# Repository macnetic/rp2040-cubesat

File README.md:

# rp2040-cubesat

> [!NOTE]  
> Preview this project on your browser with [KiCanvas](https://kicanvas.org/?github=https%3A%2F%2Fgithub.com%2Fmacnetic%2Frp2040-cubesat)!

## Requirements

| ID  | DESCRIPTION |
|-----|-------------|
| 001 | Device shall include a minimum of one RP2040 integrated circuit. |
| 002 | Dimensions shall conform with PCI/104 form factor. |
| 003 | Device shall supply 1 external UART interface. |
| 004 | Device shall supply 1 external CAN interface. |
| 005 | Device shall supply 1 on-board SPI interface. |
| 006 | Device shall supply 1 on-board I2C interface. |
| 007 | Device shall use a TCXO to generate a stable reference clock. |

## External interfaces

- UART (PHY TBD)
- CAN
- ARM CoreSight-10

## Schematic strategy

The schematics for this project is laid out across multiple sheets. 
The top-level sheets contain functional block diagrams. 
The functional circuit blocks themselves are implemented in the lower-level sheets.

## PCB Layout strategy

A 4-layer controlled impedance stackup is used.

|Layer       | Designation |
|------------|-------------|
| L1 (Top)   | SIG         |
| L2         | GND         |
| L3         | GND         |
| L3 (Bottom)| SIG+PWR     |

Functional circuit blocks are routed first. The blocks are then laid out and connected.

High-speed electrical interfaces are routed with controlled impedance transmission lines.

Priority is given to routing high-speed interfaces.

Sensitive analog circuitry is separated from digital circuitry.

## References

[1] [CubeSat Information - CubeSat.org](https://www.cubesat.org/cubesatinfo)

[2] [CubeSat Kit PCB Specification](https://web.archive.org/web/20220302180556/http://www.cubesatkit.com/docs/CSK_PCB_Spec-A5.pdf) (archived from the original at http://www.cubesatkit.com/docs/CSK_PCB_Spec-A5.pdf)

[3] [RP2040 Documentation](https://www.raspberrypi.com/documentation/microcontrollers/rp2040.html)

[4]

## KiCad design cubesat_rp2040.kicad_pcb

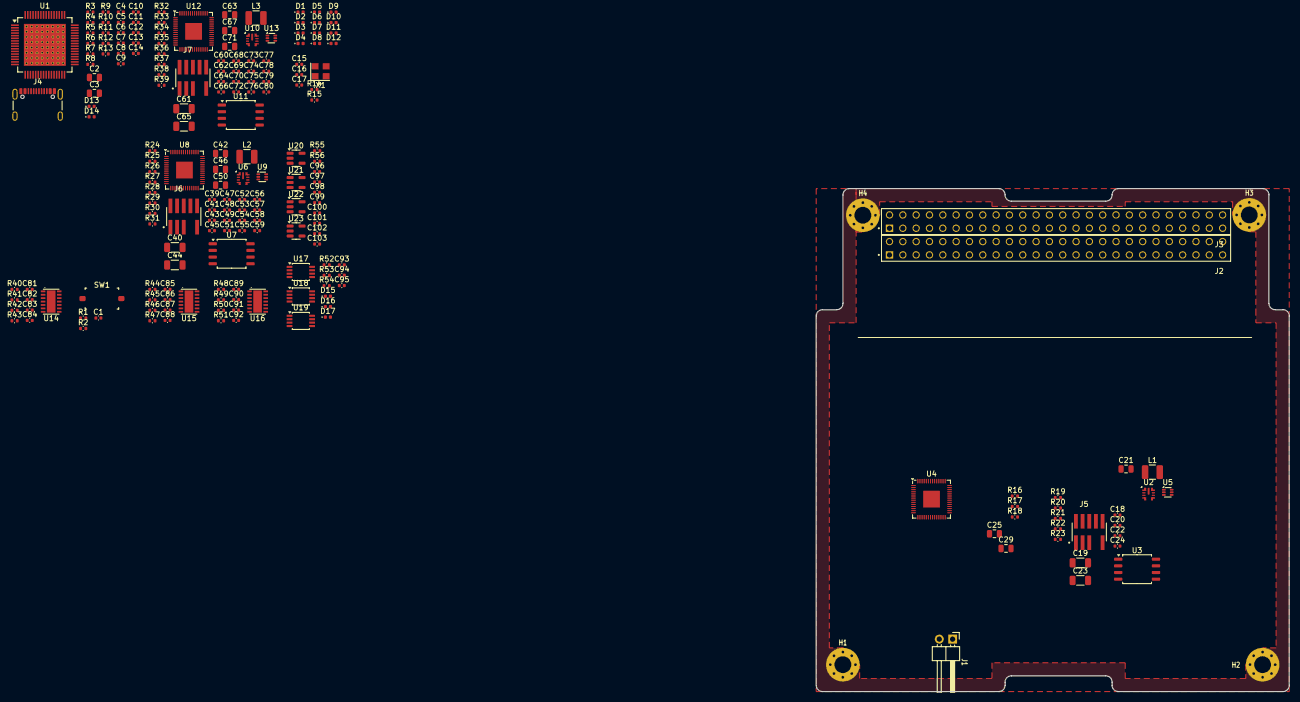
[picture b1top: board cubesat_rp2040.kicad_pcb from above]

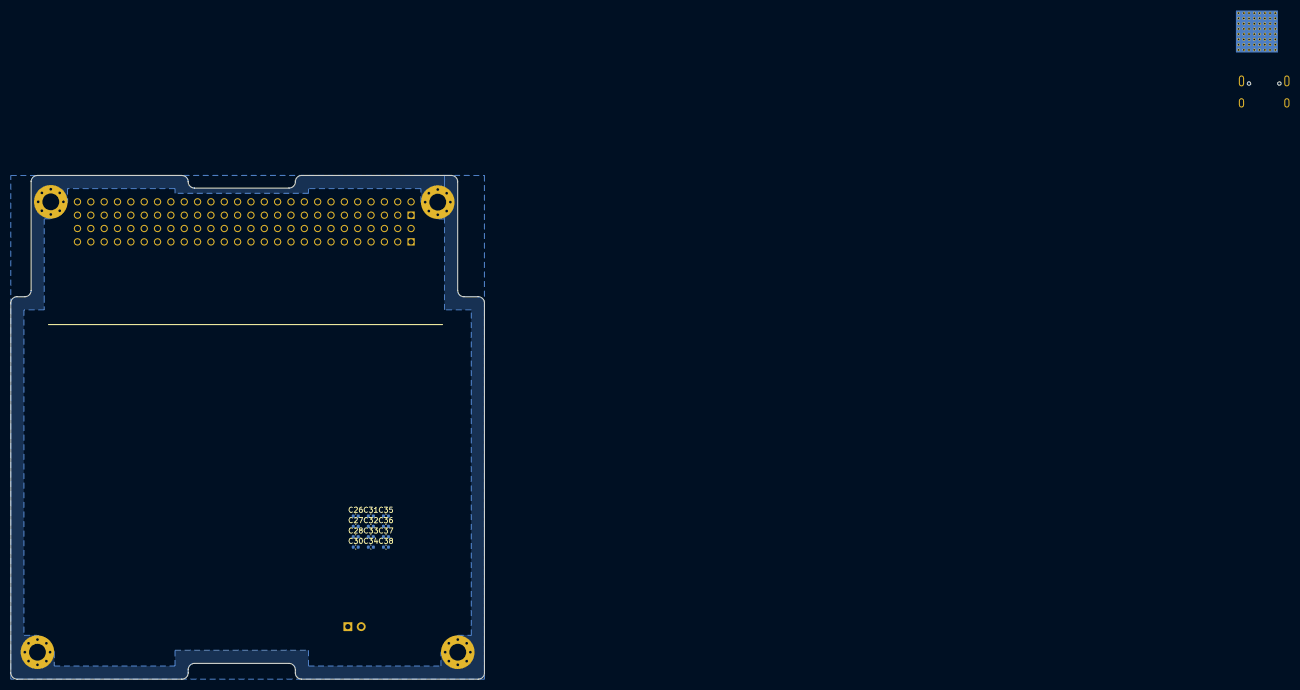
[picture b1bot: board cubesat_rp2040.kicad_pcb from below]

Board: 6 copper layers, 90.2 x 95.9 mm, 215 parts (12 on the bottom side), 138 nets, no tracks yet.

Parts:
C1, C4, C5, C6, C7, C8, C9, C10, C11, C12, C13, C14, C15, C16, C18, C20, C22, C24, C26, C27, C28, C30, C31, C32, C33, C34, C35, C36, C37, C38, C39, C41, C43, C45, C47, C48, C49, C51, C52, C53, C54, C55, C56, C57, C58, C59, C60, C62, C64, C66, C68, C69, C70, C72, C73, C74, C75, C76, C77, C78, C79, C80, C81, C82, C85, C86, C89, C90, C93, C94, C95, C96, C97, C98, C99: 100nF; C_0402_1005Metric
C2, C3, C21, C25, C29, C42, C46, C50, C63, C67, C71: 1uF; C_0805_2012Metric
C17: 15pF; C_0402_1005Metric
C19, C23, C40, C44, C61, C65: 10uF; C_1206_3216Metric
C83, C84, C87, C88, C91, C92: 4.7nF; C_0402_1005Metric
C100, C101, C102, C103: 1nF; C_0402_1005Metric
D1, D2, D3, D4, D5, D6, D7, D8, D9, D10, D11, D12, D13, D14: D_TVS; D_0402_1005Metric
D15, D16, D17: RED; LED_0402_1005Metric
H1, H2, H3, H4: MountingHole_Pad; MountingHole_3.2mm_M3_Pad_Via
J1: Conn_01x02; PinHeader_1x02_P2.54mm_Horizontal
J2, J3: ESQ-126-39-G-D; SAMTEC_ESQ-126-39-G-D_CUBESAT
J4: USB_C_Receptacle_USB2.0; USB_C_Receptacle_GCT_USB4105-xx-A_16P_TopMnt_Horizontal
J5, J6, J7: FTSH-105-01-L-DV-007-K; SAMTEC_FTSH-105-01-L-DV-007
L1, L2, L3: 15uH; L_1210_3225Metric
R1, R19, R20, R21, R22, R23, R27, R28, R29, R30, R31, R35, R36, R37, R38, R39: 100kR; R_0402_1005Metric
R2: 10kR; R_0402_1005Metric
R3, R4: 5.1kR 10%; R_0402_1005Metric
R5: 90.9kR 1%; R_0402_1005Metric
R6, R9, R10, R11, R12, R13: 4.7kR; R_0402_1005Metric
R7: 10kR 1%; R_0402_1005Metric
R8: 9.53kR 1%; R_0402_1005Metric
R14: 33R; R_0402_1005Metric
R15: 88.7R; R_0402_1005Metric
R16, R24, R32: 1kR; R_0402_1005Metric
R17, R18, R25, R26, R33, R34: 27R; R_0402_1005Metric
R40, R41, R42, R43, R44, R45, R46, R47, R48, R49, R50, R51: 60R; R_0402_1005Metric
R52, R53, R54: 470R; R_0402_1005Metric
R55, R56: 100R; R_0402_1005Metric
SW1: SW_Push; SW_Push_SPST_XKB_TS-1101-X-X
U1: TUSB4041I; HTQFP-64-1EP_10x10mm_P0.5mm_EP8x8mm_Mask4.4x4.4mm_ThermalVi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
U2, U6, U10: LMR36503MSC3RPERQ1; TI_VQFN-HR_2.1x2.1mm_P0.5mm
U3, U7, U11: IS25LP128F; SOIC-8_5.275x5.275mm_P1.27mm
U4, U8, U12: RP2040; QFN-56-1EP_7x7mm_P0.4mm_EP3.2x3.2mm
U5, U9, U13: 74LVC1G11; SOT-563
U14, U15, U16: TCAN1048AV-Q1; SOT1086-2_HVSON14_4.5x3x0.85mm_P0.65mm
U17, U18, U19: 74LVC2G38; TSSOP-8_3x3mm_P0.65mm
U20, U21: SN65LVDS1DBV; SOT-23-5
U22, U23: SN65LVDS2DBV; SOT-23-5
X1: YSO140TC; Oscillator_SMD_YXC_YSO140TC_4Pin_3.2x2.5mm

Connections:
+1V1: C2.1, C4.1, C5.1, C6.1, C7.1, C8.1, C9.1, C10.1, U1.19 (VDD), U1.25 (VDD), U1.37 (VDD), U1.45 (VDD), U1.53 (VDD), U1.60 (VDD), U1.63 (VDD)
+3V3: C3.1, C11.1, C12.1, C13.1, C14.1, C82.1, C86.1, C90.1, C93.1, C94.1, C95.1, R1.1, R14.1, R52.1, R53.1, R54.1, U1.2 (VDD33), U1.20 (VDD33), U1.31 (VDD33), U1.48 (VDD33), U14.11 (VIO), U15.11 (VIO), U16.11 (VIO), U17.8 (VCC), U18.8 (VCC), U19.8 (VCC)
+5V: C81.1, C85.1, C89.1, U14.3 (VCC), U15.3 (VCC), U16.3 (VCC)
/BOOTSEL: J1.1, R16.2, R24.2, R32.2
/CAN PHY - UNIT A/CAN_A.N: D2.2 (A2), J2.01, R41.1, R45.1, R49.1, U14.12 (CANL1), U15.12 (CANL1), U16.12 (CANL1)
/CAN PHY - UNIT A/CAN_A.P: D1.2 (A2), J2.03, R40.1, R44.1, R48.1, U14.13 (CANH1), U15.13 (CANH1), U16.13 (CANH1)
/CAN PHY - UNIT A/CAN_A.RXD: U4.16 (GPIO13), U14.4 (RXD1)
/CAN PHY - UNIT A/CAN_A.TXD: U4.17 (GPIO14), U14.1 (TXD1)
/CAN PHY - UNIT A/CAN_A.~STB: U4.18 (GPIO15), U14.14 (~STB1)
/CAN PHY - UNIT A/CAN_B.N: D4.2 (A2), J2.02, R43.1, R47.1, R51.1, U14.9 (CANL2), U15.9 (CANL2), U16.9 (CANL2)
/CAN PHY - UNIT A/CAN_B.P: D3.2 (A2), J2.04, R42.1, R46.1, R50.1, U14.10 (CANH2), U15.10 (CANH2), U16.10 (CANH2)
/CAN PHY - UNIT A/CAN_B.RXD: U4.14 (GPIO11), U14.7 (RXD2)
/CAN PHY - UNIT A/CAN_B.TXD: U4.15 (GPIO12), U14.6 (TXD2)
/CAN PHY - UNIT A/CAN_B.~STB: U4.13 (GPIO10), U14.8 (~STB2)
/CAN PHY - UNIT B/CAN_A.RXD: U8.16 (GPIO13), U15.4 (RXD1)
/CAN PHY - UNIT B/CAN_A.TXD: U8.17 (GPIO14), U15.1 (TXD1)
/CAN PHY - UNIT B/CAN_A.~STB: U8.18 (GPIO15), U15.14 (~STB1)
/CAN PHY - UNIT B/CAN_B.RXD: U8.14 (GPIO11), U15.7 (RXD2)
/CAN PHY - UNIT B/CAN_B.TXD: U8.15 (GPIO12), U15.6 (TXD2)
/CAN PHY - UNIT B/CAN_B.~STB: U8.13 (GPIO10), U15.8 (~STB2)
/CAN PHY - UNIT C/CAN_A.RXD: U12.16 (GPIO13), U16.4 (RXD1)
/CAN PHY - UNIT C/CAN_A.TXD: U12.17 (GPIO14), U16.1 (TXD1)
/CAN PHY - UNIT C/CAN_A.~STB: U12.18 (GPIO15), U16.14 (~STB1)
/CAN PHY - UNIT C/CAN_B.RXD: U12.14 (GPIO11), U16.7 (RXD2)
/CAN PHY - UNIT C/CAN_B.TXD: U12.15 (GPIO12), U16.6 (TXD2)
/CAN PHY - UNIT C/CAN_B.~STB: U12.13 (GPIO10), U16.8 (~STB2)
/Cubesat System Bus/+3V3: J2.27, J2.28
/Cubesat System Bus/+5V: J2.25, J2.26, J3.25, J3.26
/Cubesat System Bus/CHARGE: J2.31, J2.32
/Cubesat System Bus/UART_A.D+: D5.2 (A2), J2.05
/Cubesat System Bus/UART_A.D-: D6.2 (A2), J2.07
/Cubesat System Bus/UART_B.D+: D7.2 (A2), J2.06
/Cubesat System Bus/UART_B.D-: D8.2 (A2), J2.08
/Cubesat System Bus/UART_C.D+: D9.2 (A2), J2.13
/Cubesat System Bus/UART_C.D-: D10.2 (A2), J2.15
/Cubesat System Bus/UART_D.D+: D11.2 (A2), J2.22
/Cubesat System Bus/UART_D.D-: D12.2 (A2), J2.24
/Cubesat System Bus/VBAT: J3.45, J3.46
/LVDS/+3V3_UNIT: C96.1, C97.1, C98.1, C99.1, C100.1, C101.1, C102.1, C103.1, U20.1 (V_{CC}), U21.1 (V_{CC}), U22.1 (V_{CC}), U23.1 (V_{CC})
/LVDS/LVDS_RX_A.N: R55.2, U22.4 (B)
/LVDS/LVDS_RX_A.P: R55.1, U22.3 (A)
/LVDS/LVDS_RX_B.N: R56.2, U23.4 (B)
/LVDS/LVDS_RX_B.P: R56.1, U23.3 (A)
/Oscillator/24M0_CLK: C17.2, R15.2, U1.30 (XI), U4.20 (XIN), U8.20 (XIN), U12.20 (XIN)
/RP2040 - Unit A/+1V1_UNIT: C25.1, C26.1, C27.1, C28.1, U4.23 (DVDD), U4.45 (VREG_VOUT), U4.50 (DVDD)
/RP2040 - Unit A/+3V3_UNIT: C18.1, C23.1, C24.1, C29.1, C30.1, C31.1, C32.1, C33.1, C34.1, C35.1, C36.1, C37.1, C38.1, J5.01 (VTREF), L1.2, R19.2, R21.1, R22.1, R23.1, U2.8 (FB), U3.8 (VCC), U4.1 (IOVDD), U4.10 (IOVDD), U4.22 (IOVDD), U4.33 (IOVDD), U4.42 (IOVDD), U4.43 (ADC_AVDD), U4.44 (VREG_VIN), U4.48 (USB_VDD), U4.49 (IOVDD), U5.5 (VCC)
/RP2040 - Unit A/BOOT: C22.1, U2.6 (BOOT)
/RP2040 - Unit A/QSPI.SCLK: U3.6 (SCK), U4.52 (QSPI_SCLK)
/RP2040 - Unit A/QSPI.SD0: U3.5 (SI/IO0), U4.53 (QSPI_SD0)
/RP2040 - Unit A/QSPI.SD1: U3.2 (SO/IO1), U4.55 (QSPI_SD1)
/RP2040 - Unit A/QSPI.SD2: U3.3 (~WP/IO2), U4.54 (QSPI_SD2)
/RP2040 - Unit A/QSPI.SD3: U3.7 (~HOLD/IO3), U4.51 (QSPI_SD3)
/RP2040 - Unit A/QSPI.~SS: R16.1, U3.1 (~CE), U4.56 (QSPI_SS)
/RP2040 - Unit A/RP_USB.D+: R17.2, U4.47 (USB_DP)
/RP2040 - Unit A/RP_USB.D-: R18.2, U4.46 (USB_DM)
/RP2040 - Unit A/SW: C22.2, L1.1, U2.5 (SW)
/RP2040 - Unit A/SWCLK: J5.04 (TCK/SWCLK), R20.2, U4.24 (SWCLK)
/RP2040 - Unit A/SWDIO: J5.02 (TMS/SWDIO), R19.1, U4.25 (SWD)
/RP2040 - Unit A/TMR_VOTE_1: U4.38 (GPIO26_ADC0), U17.5, U18.1
/RP2040 - Unit A/TMR_VOTE_2: U4.39 (GPIO27_ADC1), U18.5, U19.1
/RP2040 - Unit A/USB.D+: R17.1, U1.56 (USB_DP_DN4)
/RP2040 - Unit A/USB.D-: R18.1, U1.57 (USB_DM_DN4)
/RP2040 - Unit A/~PWR_RESET: R22.2, U2.2 (PGOOD), U5.1
/RP2040 - Unit A/~RESET: U4.26 (RUN), U5.4
/RP2040 - Unit B/+1V1_UNIT: C46.1, C47.1, C48.1, C49.1, U8.23 (DVDD), U8.45 (VREG_VOUT), U8.50 (DVDD)
/RP2040 - Unit B/+3V3_UNIT: C39.1, C44.1, C45.1, C50.1, C51.1, C52.1, C53.1, C54.1, C55.1, C56.1, C57.1, C58.1, C59.1, J6.01 (VTREF), L2.2, R27.2, R29.1, R30.1, R31.1, U6.8 (FB), U7.8 (VCC), U8.1 (IOVDD), U8.10 (IOVDD), U8.22 (IOVDD), U8.33 (IOVDD), U8.42 (IOVDD), U8.43 (ADC_AVDD), U8.44 (VREG_VIN), U8.48 (USB_VDD), U8.49 (IOVDD), U9.5 (VCC)
/RP2040 - Unit B/BOOT: C43.1, U6.6 (BOOT)
/RP2040 - Unit B/QSPI.SCLK: U7.6 (SCK), U8.52 (QSPI_SCLK)
/RP2040 - Unit B/QSPI.SD0: U7.5 (SI/IO0), U8.53 (QSPI_SD0)
/RP2040 - Unit B/QSPI.SD1: U7.2 (SO/IO1), U8.55 (QSPI_SD1)
/RP2040 - Unit B/QSPI.SD2: U7.3 (~WP/IO2), U8.54 (QSPI_SD2)
/RP2040 - Unit B/QSPI.SD3: U7.7 (~HOLD/IO3), U8.51 (QSPI_SD3)
/RP2040 - Unit B/QSPI.~SS: R24.1, U7.1 (~CE), U8.56 (QSPI_SS)
/RP2040 - Unit B/RP_USB.D+: R25.2, U8.47 (USB_DP)
/RP2040 - Unit B/RP_USB.D-: R26.2, U8.46 (USB_DM)
/RP2040 - Unit B/SW: C43.2, L2.1, U6.5 (SW)
/RP2040 - Unit B/SWCLK: J6.04 (TCK/SWCLK), R28.2, U8.24 (SWCLK)
/RP2040 - Unit B/SWDIO: J6.02 (TMS/SWDIO), R27.1, U8.25 (SWD)
/RP2040 - Unit B/TMR_VOTE_1: U8.38 (GPIO26_ADC0), U17.1, U19.5
/RP2040 - Unit B/TMR_VOTE_2: U8.39 (GPIO27_ADC1), U18.6, U19.2
/RP2040 - Unit B/USB.D+: R25.1, U1.49 (USB_DP_DN3)
/RP2040 - Unit B/USB.D-: R26.1, U1.50 (USB_DM_DN3)
/RP2040 - Unit B/~PWR_RESET: R30.2, U6.2 (PGOOD), U9.1
/RP2040 - Unit B/~RESET: U8.26 (RUN), U9.4
/RP2040 - Unit C/+1V1_UNIT: C67.1, C68.1, C69.1, C70.1, U12.23 (DVDD), U12.45 (VREG_VOUT), U12.50 (DVDD)
/RP2040 - Unit C/+3V3_UNIT: C60.1, C65.1, C66.1, C71.1, C72.1, C73.1, C74.1, C75.1, C76.1, C77.1, C78.1, C79.1, C80.1, J7.01 (VTREF), L3.2, R35.2, R37.1, R38.1, R39.1, U10.8 (FB), U11.8 (VCC), U12.1 (IOVDD), U12.10 (IOVDD), U12.22 (IOVDD), U12.33 (IOVDD), U12.42 (IOVDD), U12.43 (ADC_AVDD), U12.44 (VREG_VIN), U12.48 (USB_VDD), U12.49 (IOVDD), U13.5 (VCC)
/RP2040 - Unit C/BOOT: C64.1, U10.6 (BOOT)
/RP2040 - Unit C/QSPI.SCLK: U11.6 (SCK), U12.52 (QSPI_SCLK)
/RP2040 - Unit C/QSPI.SD0: U11.5 (SI/IO0), U12.53 (QSPI_SD0)
/RP2040 - Unit C/QSPI.SD1: U11.2 (SO/IO1), U12.55 (QSPI_SD1)
/RP2040 - Unit C/QSPI.SD2: U11.3 (~WP/IO2), U12.54 (QSPI_SD2)
/RP2040 - Unit C/QSPI.SD3: U11.7 (~HOLD/IO3), U12.51 (QSPI_SD3)
/RP2040 - Unit C/QSPI.~SS: R32.1, U11.1 (~CE), U12.56 (QSPI_SS)
/RP2040 - Unit C/RP_USB.D+: R33.2, U12.47 (USB_DP)
/RP2040 - Unit C/RP_USB.D-: R34.2, U12.46 (USB_DM)
/RP2040 - Unit C/SW: C64.2, L3.1, U10.5 (SW)
/RP2040 - Unit C/SWCLK: J7.04 (TCK/SWCLK), R36.2, U12.24 (SWCLK)
/RP2040 - Unit C/SWDIO: J7.02 (TMS/SWDIO), R35.1, U12.25 (SWD)
/RP2040 - Unit C/TMR_VOTE_1: U12.38 (GPIO26_ADC0), U17.2, U19.6
/RP2040 - Unit C/TMR_VOTE_2: U12.39 (GPIO27_ADC1), U17.6, U18.2
/RP2040 - Unit C/USB.D+: R33.1, U1.41 (USB_DP_DN2)
/RP2040 - Unit C/USB.D-: R34.1, U1.42 (USB_DM_DN2)
/RP2040 - Unit C/~PWR_RESET: R38.2, U10.2 (PGOOD), U13.1
/RP2040 - Unit C/~RESET: U12.26 (RUN), U13.4
/TMR/~TMR_RESET_A: D15.1 (K), R23.2, U5.6, U17.7, U19.3
/TMR/~TMR_RESET_B: D16.1 (K), R31.2, U9.6, U17.3, U18.7
/TMR/~TMR_RESET_C: D17.1 (K), R39.2, U13.6, U18.3, U19.7
/USB/PWRCTL1/BATEN1: R13.1, U1.4 (PWRCTL1/BATEN1)
/USB/PWRCTL2/BATEN2: R12.1, U1.3 (PWRCTL2/BATEN2)
/USB/PWRCTL3/BATEN3: R11.1, U1.1 (PWRCTL3/BATEN3)
/USB/PWRCTL4/BATEN4: R10.1, U1.64 (PWRCTL4/BATEN4)
/USB/USB_UP.CC1: J4.A5 (CC1), R4.1
/USB/USB_UP.CC2: J4.B5 (CC2), R3.1
/USB/USB_UP.D+: D13.2 (A2), J4.A6 (D+), J4.B6 (D+), U1.21 (USB_DP_UP)
/USB/USB_UP.D-: D14.2 (A2), J4.A7 (D-), J4.B7 (D-), U1.22 (USB_DM_UP)
/USB/USB_VBUS: R5.2, R7.1, U1.16 (USB_VBUS)
/~USR_RESET: C1.1, J5.10 (nSRST), J6.10 (nSRST), J7.10 (nSRST), R2.1, R21.2, R29.2, R37.2, U1.18 (GRSTz), U5.3, U9.3, U13.3
GND: C1.2, C2.2, C3.2, C4.2, C5.2, C6.2, C7.2, C8.2, C9.2, C10.2, C11.2, C12.2, C13.2, C14.2, C15.2, C17.1, C18.2, C19.2, C20.2, C21.2, C23.2, C24.2, C25.2, C26.2, C27.2, C28.2, C29.2, C30.2, C31.2, C32.2, C33.2, C34.2, C35.2, C36.2, C37.2, C38.2, C39.2, C40.2, C41.2, C42.2, C44.2, C45.2, C46.2, C47.2, C48.2, C49.2, C50.2, C51.2, C52.2, C53.2, C54.2, C55.2, C56.2, C57.2, C58.2, C59.2, C60.2, C61.2, C62.2, C63.2, C65.2, C66.2, C67.2, C68.2, C69.2, C70.2, C71.2, C72.2, C73.2, C74.2, C75.2, C76.2, C77.2, C78.2, C79.2, C80.2, C81.2, C82.2, C83.1, C84.1, C85.2, C86.2, C87.1, C88.1, C89.2, C90.2, C91.1, C92.1, C93.2, C94.2, C95.2, C96.2, C97.2, C98.2, C99.2, C100.2, C101.2, C102.2, C103.2, D1.1 (A1), D2.1 (A1), D3.1 (A1), D4.1 (A1), D5.1 (A1), D6.1 (A1), D7.1 (A1), D8.1 (A1), D9.1 (A1), D10.1 (A1), D11.1 (A1), D12.1 (A1), D13.1 (A1), D14.1 (A1), H1.1, H2.1, H3.1, H4.1, J1.2, J2.33, J2.34, J3.29, J3.30, J3.31, J3.32, J4.A1 (GND), J4.A12 (GND), J4.B1 (GND), J4.B12 (GND), J4.S1 (SHIELD), J5.03 (GND), J5.05 (GND), J5.09 (GND), J6.03 (GND), J6.05 (GND), J6.09 (GND), J7.03 (GND), J7.05 (GND), J7.09 (GND), R3.2, R4.2, R6.2, R7.2, R8.2, R9.2, R10.2, R11.2, R12.2, R13.2, R20.1, R28.1, R36.1, SW1.1, U1.65 (VSS), U2.9 (GND), U3.4 (GND), U4.57 (GND), U5.2 (GND), U6.9 (GND), U7.4 (GND), U8.57 (GND), U9.2 (GND), U10.9 (GND), U11.4 (GND), U12.57 (GND), U13.2 (GND), U14.2 (GND), U14.5 (GND), U14.15 (EP), U15.2 (GND), U15.5 (GND), U15.15 (EP), U16.2 (GND), U16.5 (GND), U16.15 (EP), U17.4 (GND), U18.4 (GND), U19.4 (GND), U20.2 (GND), U21.2 (GND), U22.2 (GND), U23.2 (GND), X1.2 (GND)
unnamed: C16.2, R15.1
unnamed: C83.2, R40.2, R41.2
unnamed: C84.2, R42.2, R43.2
unnamed: C87.2, R44.2, R45.2
unnamed: C88.2, R46.2, R47.2
unnamed: C91.2, R48.2, R49.2
unnamed: C92.2, R50.2, R51.2
unnamed: D15.2 (A), R52.2
unnamed: D16.2 (A), R53.2
unnamed: D17.2 (A), R54.2
unnamed: R1.2, R2.2, SW1.2
unnamed: R9.1, U1.13 (AUTOENz/HS_SUSPEND)
unnamed: R6.1, U1.10 (GANGED/SMBA2/HS_UP)
unnamed: R8.1, U1.32 (USB_R1)
unnamed: C21.1, U2.1 (MODE/SYNC), U2.7 (VCC)
unnamed: C42.1, U6.1 (MODE/SYNC), U6.7 (VCC)
unnamed: C63.1, U10.1 (MODE/SYNC), U10.7 (VCC)
unnamed: C16.1, X1.3 (OUT)
unnamed: C15.1, R14.2, X1.4 (Vdd)
VBUS: C19.1, C20.1, C40.1, C41.1, C61.1, C62.1, J4.A4 (VBUS), J4.A9 (VBUS), J4.B4 (VBUS), J4.B9 (VBUS), R5.1, U2.3 (EN/UVLO), U2.4 (VIN), U6.3 (EN/UVLO), U6.4 (VIN), U10.3 (EN/UVLO), U10.4 (VIN)

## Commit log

2024-05-14 Upload existing files
2024-06-16 Update Kicad version and remove ignored files
2024-06-21 Revert breaking expected KiCAD project structure
2024-06-23 break out subcircuits, add switching regulator
2024-06-23 Clean up project
2024-06-24 Block diagram
2024-07-02 Complete power regulator schematics
2024-07-03 Update footprints, route switching regulator circuit block
2024-07-03 Update gitignore
2024-07-03 Update footprints, route more circuit blocks
2024-07-04 Update README, change footprints
2024-07-16 Big update, bad commit messsage :)
2024-08-12 Major update, everything has been touched
2024-08-28 Another large revision, but we are getting closer
2024-09-05 More work on interfaces
